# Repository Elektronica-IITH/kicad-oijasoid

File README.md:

# Elektronica Bootcamp '25 - README

## Overview
Welcome to Elektronica, the premier Electronics and Signal Processing Club at IIT Hyderabad! This README provides details about our Bootcamp '25, how to participate, what you can gain by joining us.

## About Elektronica
Elektronica is a vibrant community where technology enthusiasts collaborate on innovative projects, explore emerging tech trends, and engage in hands-on learning. From embedded systems and signal processing to wireless communication, we cover a broad spectrum of exciting domains.

## Why Join the Elektronica Bootcamp?
By participating in the Elektronica Bootcamp, you get access to:

- 🏆 **Skill Enhancement:** Gain hands-on experience in core electronics and signal processing domains.
- 🌟 **Expert-Led Sessions:** Learn from industry professionals and experienced mentors.
- 🤝 **Personalized Mentorship:** Receive guidance, clear your doubts, and enhance your technical skills.
- 🛠️ **Real-World Projects:** Work on practical projects that solve real-world problems.
- 🚀 **Innovative Learning:** Engage in interactive workshops and hackathons.

## Bootcamp Details
- **Start Date:** Mar 22, 2025
- **Duration:** 3 weeks (every Saturday, 5:30 - 7:30)

## Sessions
1. PCB Design
2. Biomedical signal processing
3. Sensors

## Final Project
Build a smartwatch as a team. 

## Contact Us
For queries or more information, feel free to reach out:
- **Email:** elektronica@gymkhana.iith.ac.in

Don't miss this chance to upskill and innovate with Elektronica!

Best Regards,  
**Elektronica**  
IIT Hyderabad

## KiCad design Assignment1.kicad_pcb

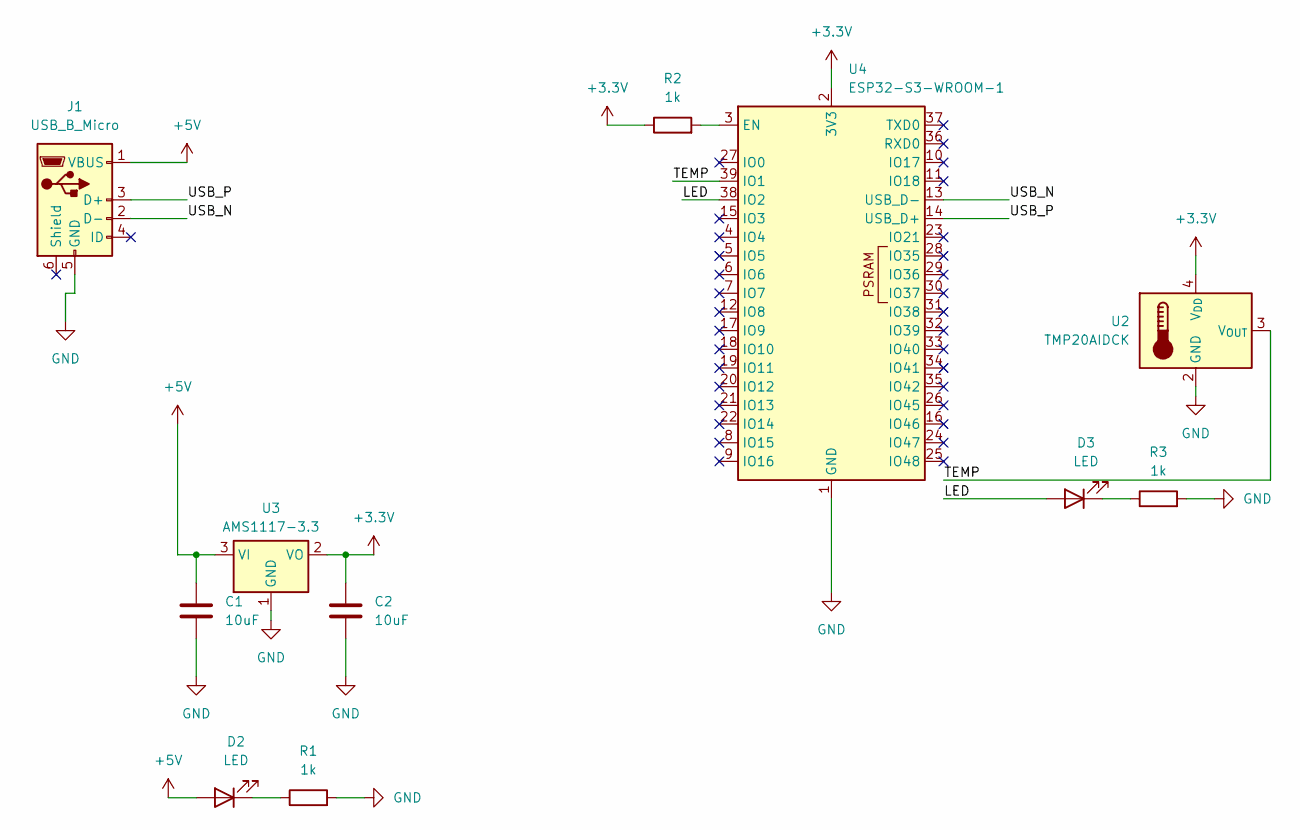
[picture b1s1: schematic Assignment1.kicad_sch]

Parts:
C1, C2: 10uF; C_0201_0603Metric
D2, D3: LED; LED_0201_0603Metric
J1: USB_B_Micro; USB_Micro-B_Amphenol_10118194-0001LF_Horizontal
R1, R2, R3: 1k; R_0201_0603Metric
U2: TMP20AIDCK; SOT-353_SC-70-5
U3: AMS1117-3.3; SOT-223-3_TabPin2
U4: ESP32-S3-WROOM-1

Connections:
+3.3V: C2.1, R2.1, U2.4 (V_{DD}), U3.2 (VO), U4.2 (3V3)
+5V: C1.1, D2.2 (A), J1.1 (VBUS), U3.3 (VI)
/LED: D3.2 (A), U4.38 (IO2)
/TEMP: U2.3 (V_{OUT}), U4.39 (IO1)
/USB_N: J1.2 (D-), U4.13 (USB_D-)
/USB_P: J1.3 (D+), U4.14 (USB_D+)
GND: C1.2, C2.2, J1.5 (GND), R1.2, R3.2, U2.2 (GND), U2.5 (GND), U3.1 (GND), U4.1 (GND), U4.40 (GND), U4.41 (GND)
unnamed: D2.1 (K), R1.1
unnamed: D3.1 (K), R3.1
unnamed: R2.2, U4.3 (EN)

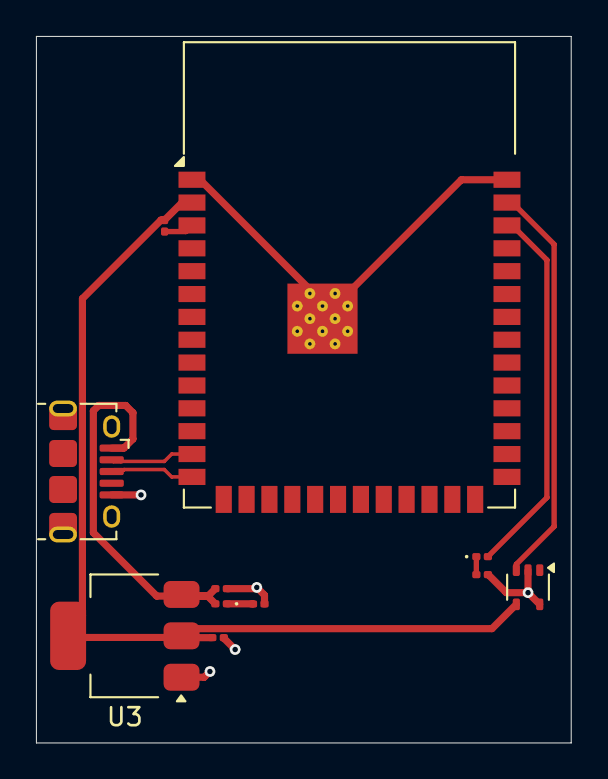
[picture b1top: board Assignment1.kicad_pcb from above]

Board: 2 copper layers, 29.7 x 39.2 mm, 11 parts (0 on the bottom side), 10 nets.

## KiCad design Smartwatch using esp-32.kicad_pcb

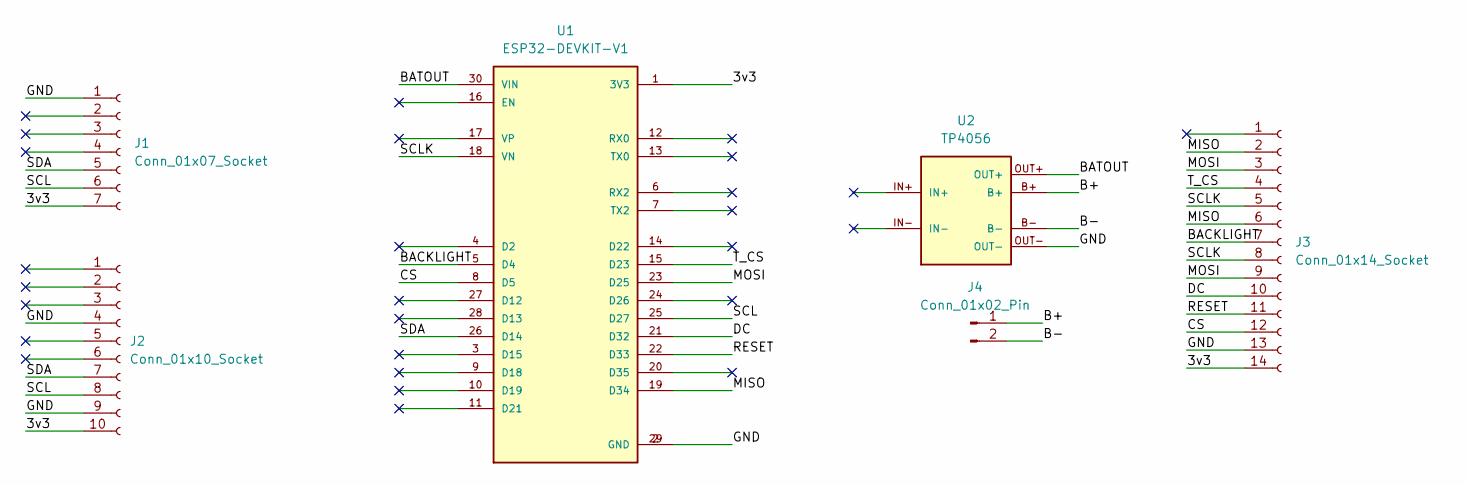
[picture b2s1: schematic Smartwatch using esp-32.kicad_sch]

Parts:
J1: Conn_01x07_Socket; PinSocket_1x07_P2.54mm_Vertical
J2: Conn_01x10_Socket; PinSocket_1x10_P2.54mm_Vertical
J3: Conn_01x14_Socket; PinSocket_1x14_P2.54mm_Vertical
J4: Conn_01x02_Pin; JST_PH_S2B-PH-K_1x02_P2.00mm_Horizontal
U1: ESP32-DEVKIT-V1; MODULE_ESP32_DEVKIT_V1; PARTREV N/A
U2: TP4056

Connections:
/3v3: J1.7, J2.10, J3.14, U1.1 (3V3)
/B+: J4.1, U2.B+
/B-: J4.2, U2.B-
/BACKLIGHT: J3.7, U1.5 (D4)
/BATOUT: U1.30 (VIN), U2.OUT+
/CS: J3.12, U1.8 (D5)
/DC: J3.10, U1.21 (D32)
/GND: J1.1, J2.4, J2.9, J3.13, U1.2 (GND), U1.29 (GND), U2.OUT-
/MISO: J3.2, J3.6, U1.19 (D34)
/MOSI: J3.3, J3.9, U1.23 (D25)
/RESET: J3.11, U1.22 (D33)
/SCL: J1.6, J2.8, U1.25 (D27)
/SCLK: J3.5, J3.8, U1.18 (VN)
/SDA: J1.5, J2.7, U1.26 (D14)
/T_CS: J3.4, U1.15 (D23)

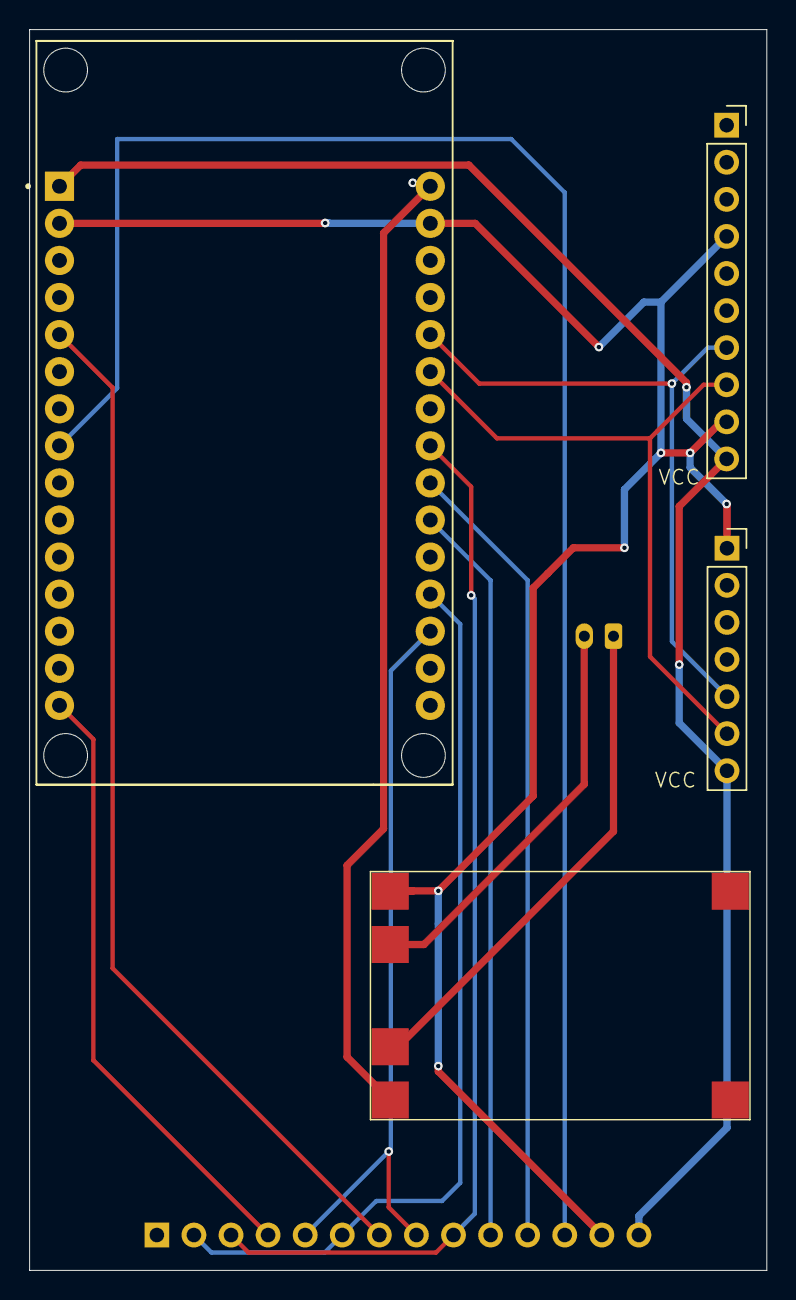
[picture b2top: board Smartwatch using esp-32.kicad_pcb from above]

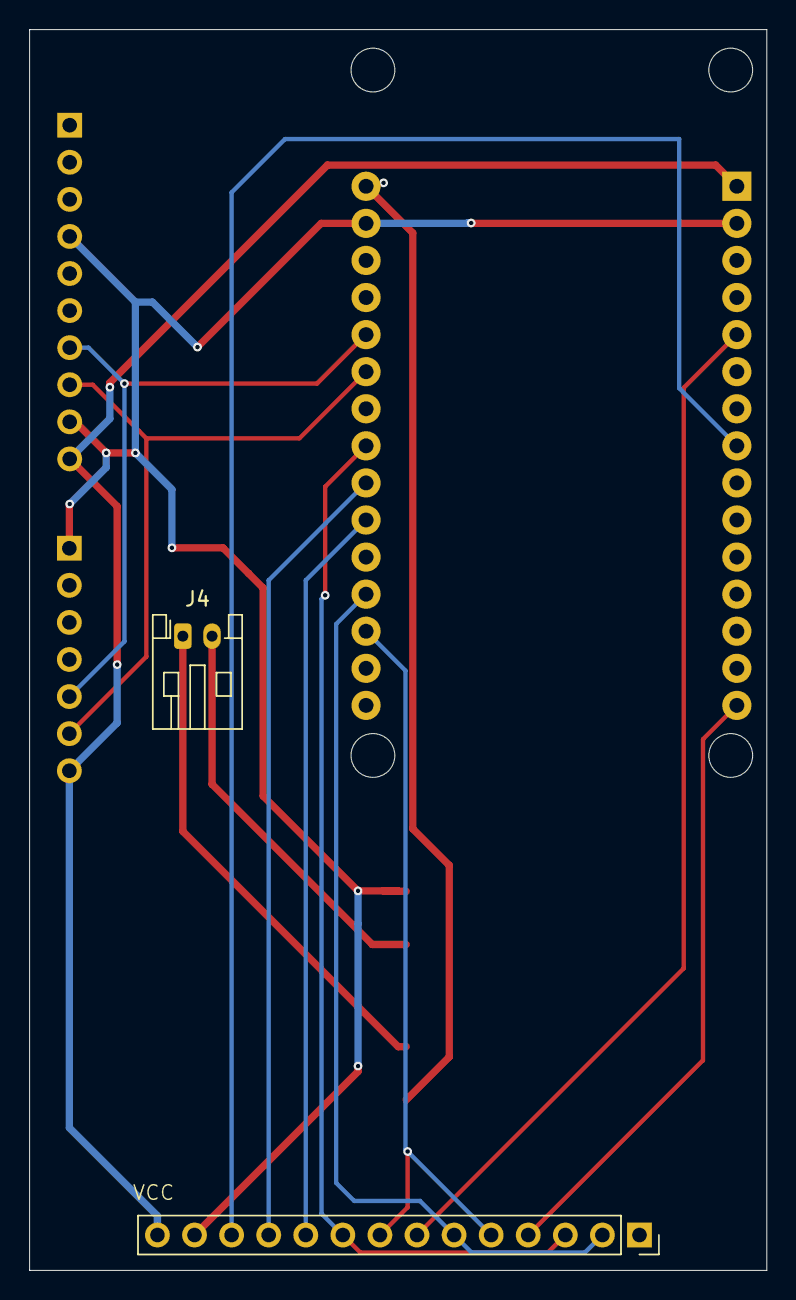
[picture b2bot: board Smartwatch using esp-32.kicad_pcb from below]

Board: 2 copper layers, 50.5 x 85.0 mm, 6 parts (2 on the bottom side), 15 nets.

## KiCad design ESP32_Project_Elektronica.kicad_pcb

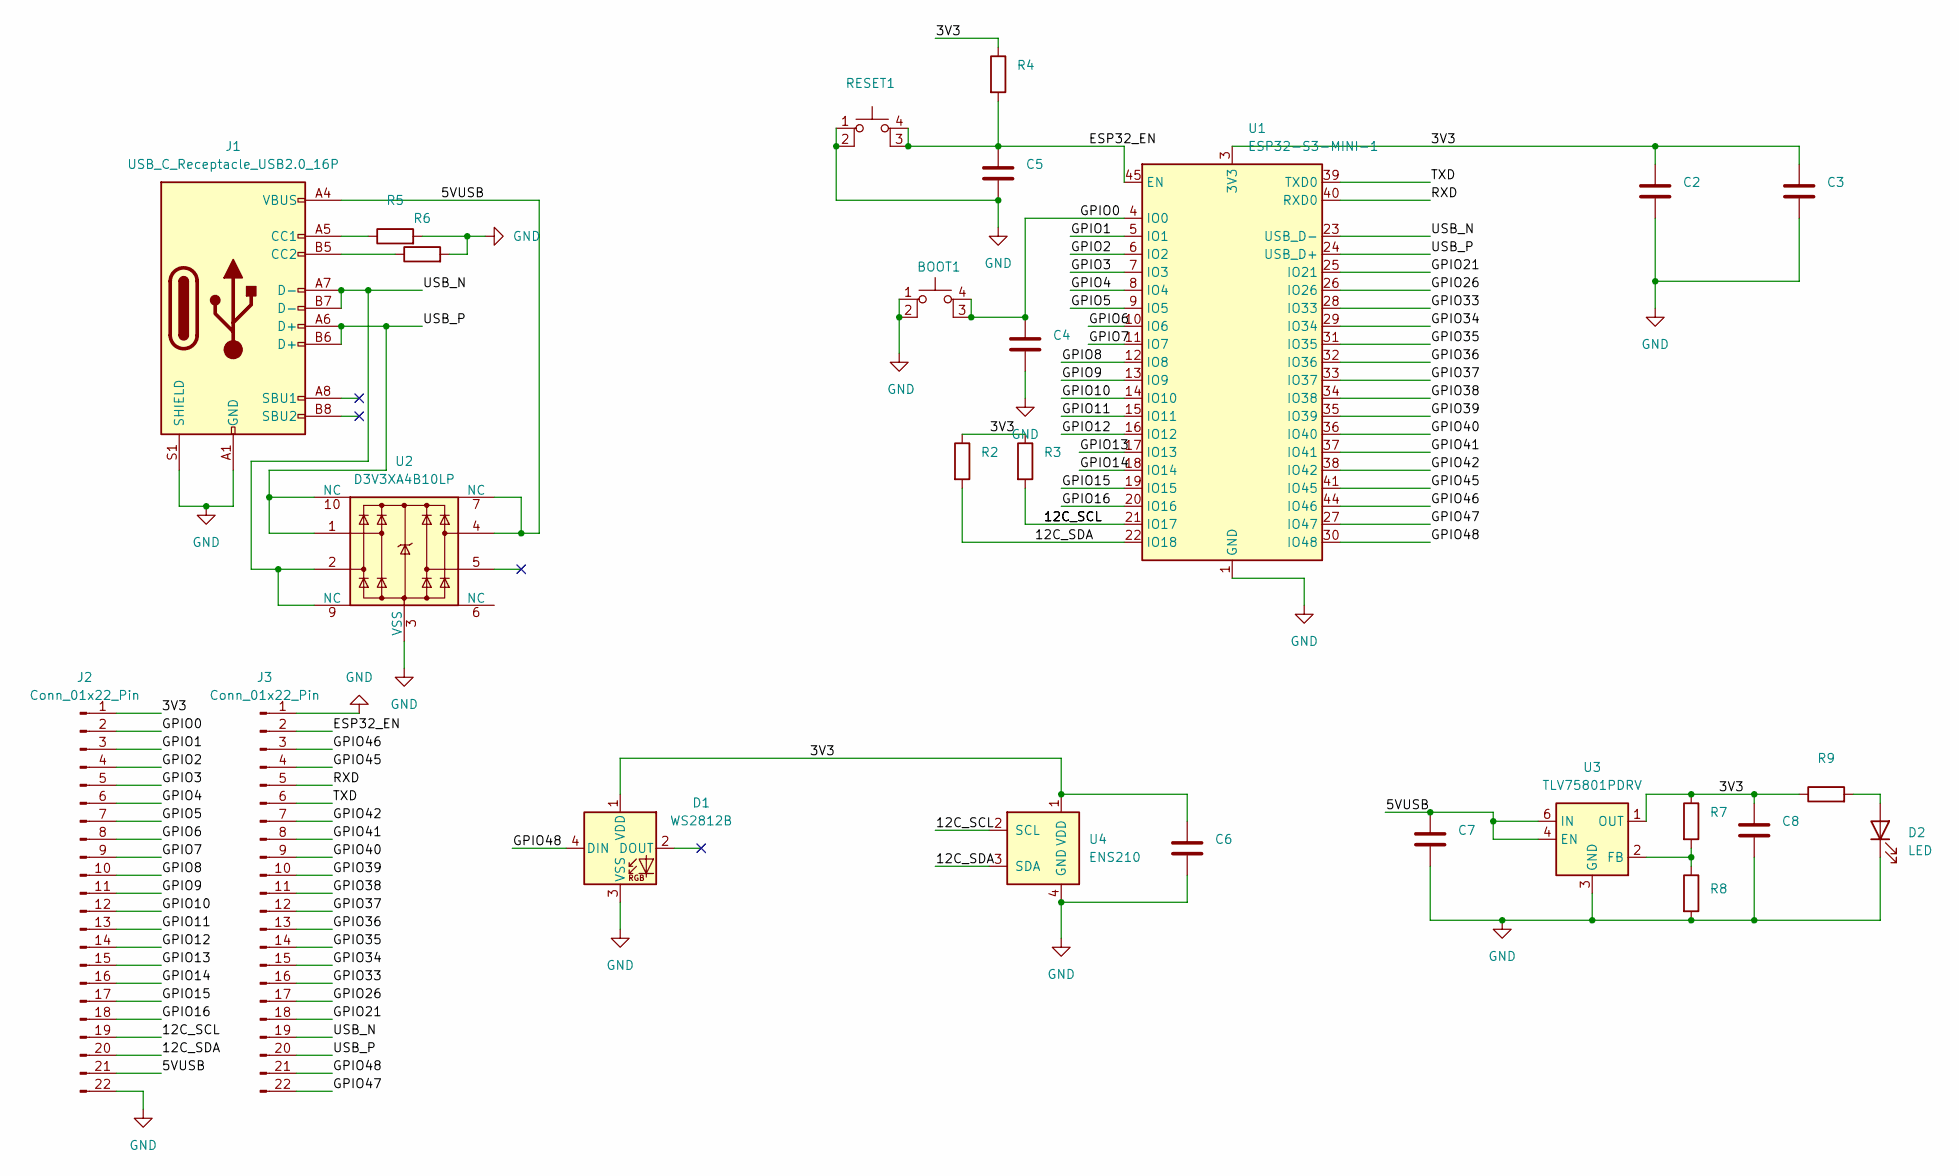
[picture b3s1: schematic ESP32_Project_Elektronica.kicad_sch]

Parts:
BOOT1: SW_MEC_5GSH9
C2, C3, C4, C5, C6, C7, C8: C_0603_1608Metric
D1: WS2812B; LED_WS2812B_PLCC4_5.0x5.0mm_P3.2mm
D2: LED; LED_0201_0603Metric_Pad0.64x0.40mm_HandSolder
J1: USB_C_Receptacle_USB2.0_16P; USB_C_Receptacle_GCT_USB4105-xx-A_16P_TopMnt_Horizontal
J2, J3: Conn_01x22_Pin; PinHeader_1x22_P2.54mm_Vertical
R2, R3, R4, R5, R6, R7, R8, R9: R_0603_1608Metric
RESET1: SW_MEC_5GSH9
U1: ESP32-S3-MINI-1; ESP32-S2-MINI-1
U2: D3V3XA4B10LP; Diodes_UDFN-10_1.0x2.5mm_P0.5mm
U3: TLV75801PDRV; WSON-6-1EP_2x2mm_P0.65mm_EP1x1.6mm
U4: ENS210; AMS_QFN-4-1EP_2x2mm_P0.95mm_EP0.7x1.6mm

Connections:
/3V3: C2.2, C3.2, C6.2, C8.2, D1.1 (VDD), J2.1, R2.1, R3.1, R4.1, R7.1, R9.1, U1.3 (3V3), U3.1 (OUT), U4.1 (VDD)
/5VUSB: C7.2, J1.A4 (VBUS), J1.A9 (VBUS), J1.B4 (VBUS), J1.B9 (VBUS), J2.21, U2.4, U2.7 (NC), U3.4 (EN), U3.6 (IN)
/12C_SDA: J2.20, R2.2, U1.22 (IO18), U4.3 (SDA)
/ESP32_EN: C5.2, J3.2, R4.2, RESET1.3 (K), RESET1.4 (A), U1.45 (EN)
/GPIO0: BOOT1.3 (K), BOOT1.4 (A), C4.2, J2.2, U1.4 (IO0)
/GPIO1: J2.3, U1.5 (IO1)
/GPIO2: J2.4, U1.6 (IO2)
/GPIO3: J2.5, U1.7 (IO3)
/GPIO4: J2.6, U1.8 (IO4)
/GPIO5: J2.7, U1.9 (IO5)
/GPIO6: J2.8, U1.10 (IO6)
/GPIO7: J2.9, U1.11 (IO7)
/GPIO8: J2.10, U1.12 (IO8)
/GPIO9: J2.11, U1.13 (IO9)
/GPIO10: J2.12, U1.14 (IO10)
/GPIO11: J2.13, U1.15 (IO11)
/GPIO12: J2.14, U1.16 (IO12)
/GPIO13: J2.15, U1.17 (IO13)
/GPIO14: J2.16, U1.18 (IO14)
/GPIO15: J2.17, U1.19 (IO15)
/GPIO16: J2.18, U1.20 (IO16)
/GPIO21: J3.18, U1.25 (IO21)
/GPIO26: J3.17, U1.26 (IO26)
/GPIO33: J3.16, U1.28 (IO33)
/GPIO34: J3.15, U1.29 (IO34)
/GPIO35: J3.14, U1.31 (IO35)
/GPIO36: J3.13, U1.32 (IO36)
/GPIO37: J3.12, U1.33 (IO37)
/GPIO38: J3.11, U1.34 (IO38)
/GPIO39: J3.10, U1.35 (IO39)
/GPIO40: J3.9, U1.36 (IO40)
/GPIO41: J3.8, U1.37 (IO41)
/GPIO42: J3.7, U1.38 (IO42)
/GPIO45: J3.4, U1.41 (IO45)
/GPIO46: J3.3, U1.44 (IO46)
/GPIO47: J3.22, U1.27 (IO47)
/GPIO48: D1.4 (DIN), J3.21, U1.30 (IO48)
/RXD: J3.5, U1.40 (RXD0)
/TXD: J3.6, U1.39 (TXD0)
/USB_N: J1.A7 (D-), J1.B7 (D-), J3.19, U1.23 (USB_D-), U2.2, U2.9 (NC)
/USB_P: J1.A6 (D+), J1.B6 (D+), J3.20, U1.24 (USB_D+), U2.1, U2.10 (NC)
GND: BOOT1.1, BOOT1.2, C2.1, C3.1, C4.1, C5.1, C6.1, C7.1, C8.1, D1.3 (VSS), D2.1 (K), J1.A1 (GND), J1.A12 (GND), J1.B1 (GND), J1.B12 (GND), J1.S1 (SHIELD), J2.22, J3.1, R5.2, R6.2, R8.2, RESET1.1, RESET1.2, U1.1 (GND), U1.2 (GND), U1.42 (GND), U1.43 (GND), U1.46 (GND), U1.47 (GND), U1.48 (GND), U1.49 (GND), U1.50 (GND), U1.51 (GND), U1.52 (GND), U1.53 (GND), U1.54 (GND), U1.55 (GND), U1.56 (GND), U1.57 (GND), U1.58 (GND), U1.59 (GND), U1.60 (GND), U1.61 (GND), U1.62 (GND), U1.63 (GND), U1.64 (GND), U1.65 (GND), U2.3 (VSS), U2.8 (VSS), U3.3 (GND), U3.7 (GND), U4.4 (GND), U4.5 (GND)
unnamed: D2.2 (A), R9.2
unnamed: J1.A5 (CC1), R5.1
unnamed: J1.B5 (CC2), R6.1
unnamed: R7.2, R8.1, U3.2 (FB)

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
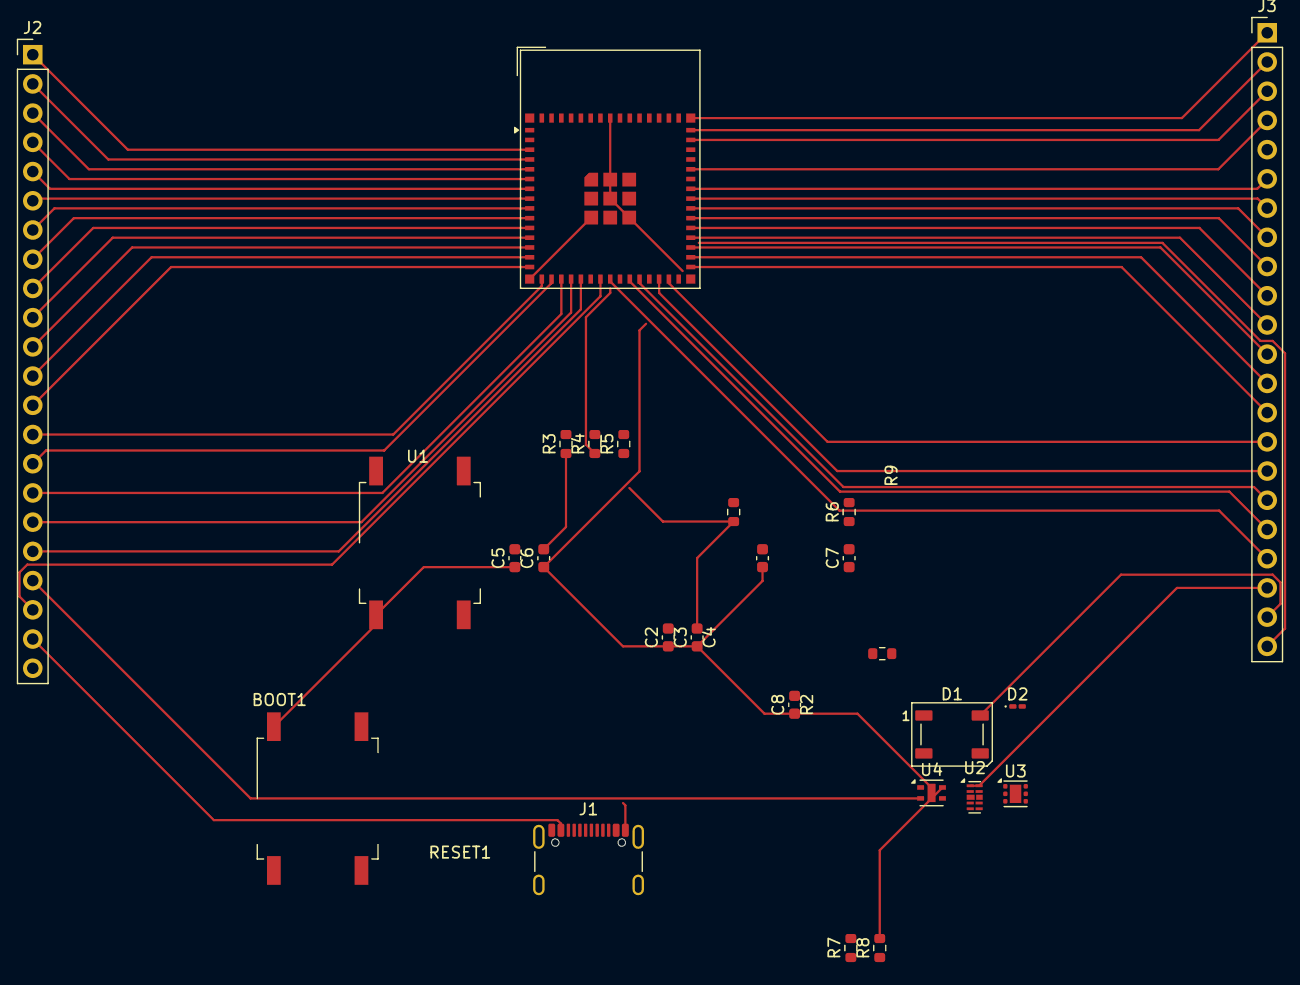
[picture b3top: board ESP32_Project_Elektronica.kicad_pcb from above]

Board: 2 copper layers, 26 parts (0 on the bottom side), 48 nets.

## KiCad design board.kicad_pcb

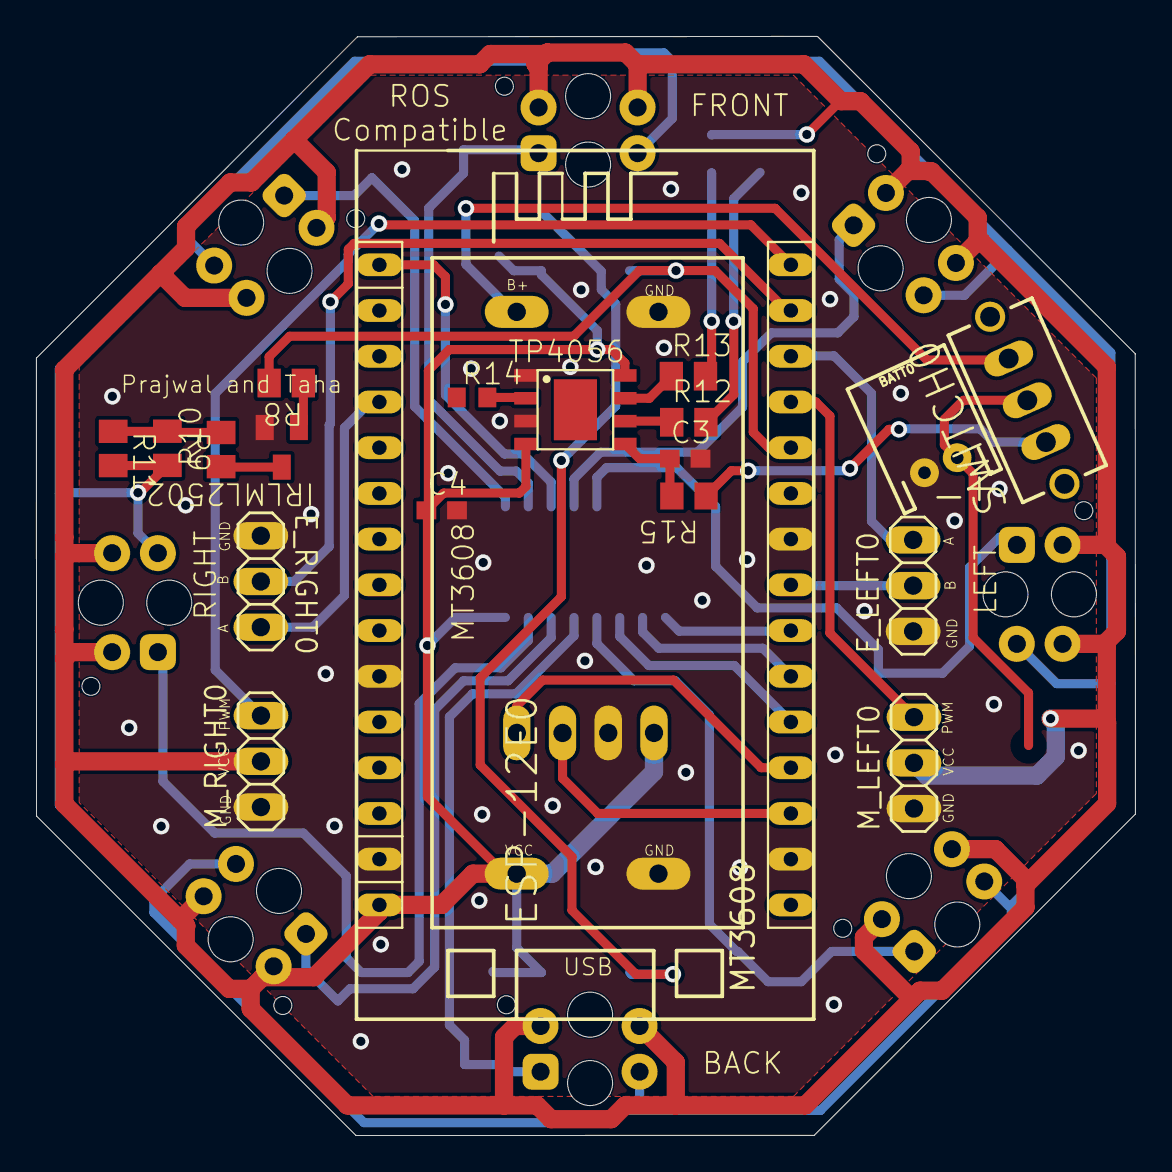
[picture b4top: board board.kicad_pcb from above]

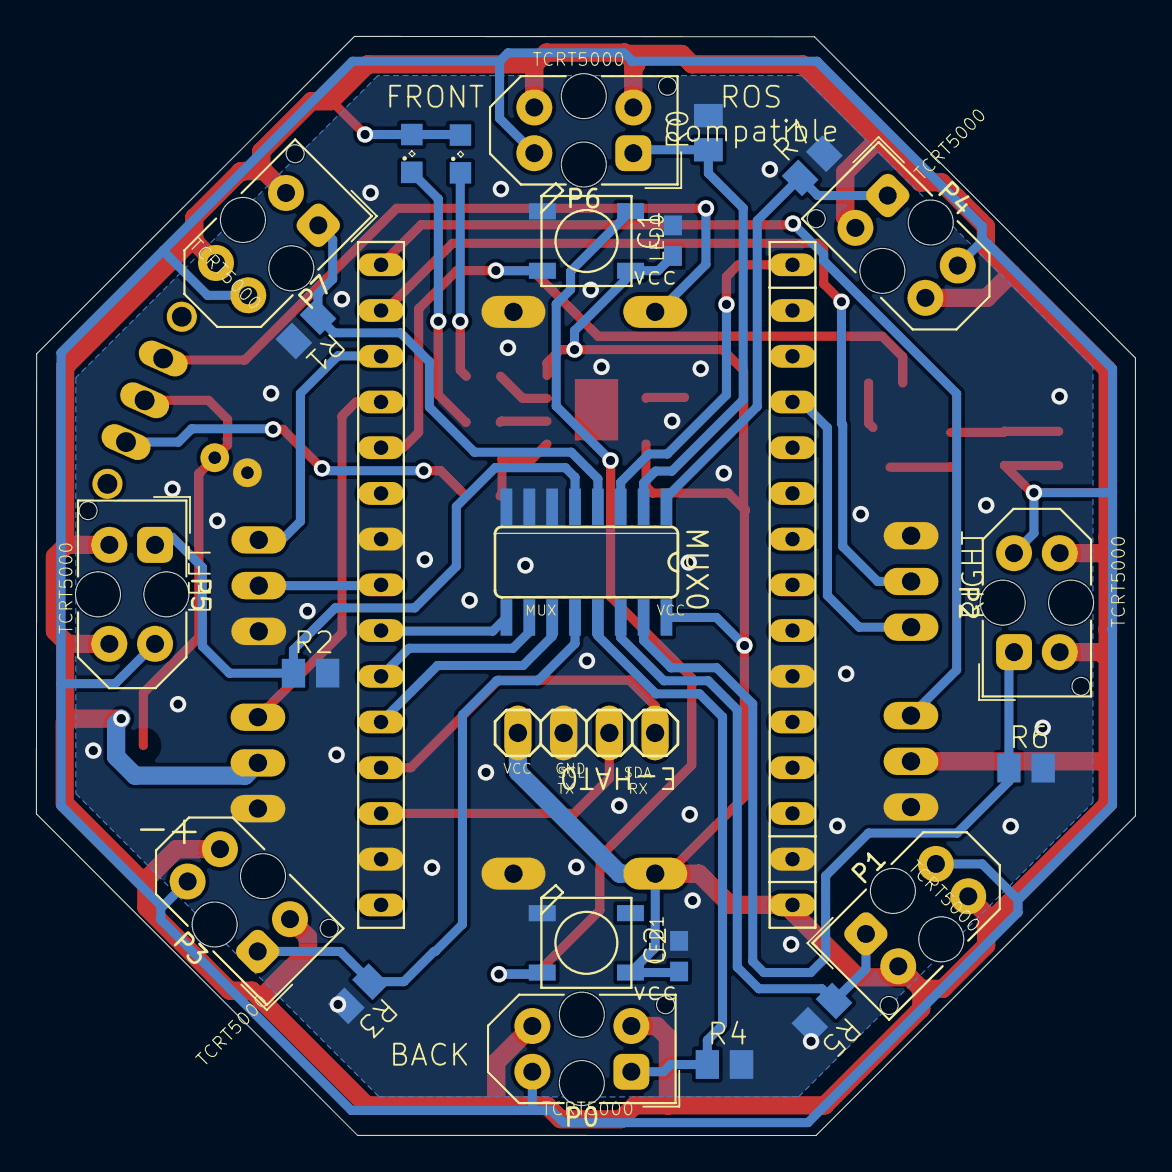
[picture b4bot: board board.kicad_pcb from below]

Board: 2 copper layers, 61.1 x 61.1 mm, 44 parts (24 on the bottom side), 37 nets.

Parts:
BATT0: CONN_02JST-PTH-2; JST-2-PTH_513
C1, C2: 0.10 nF; C0603_348
C3, C4: 10 uF; C0603_420
CHRG0: RED; SML0805_259
E-HAT0: PINHD-1X4; 1X04
ESP-12E0: ESP12E_DEVKIT
E_LEFT0: PINHD-1X3; 1X03
E_RIGHT0: PINHD-1X3; 1X03
IRLML2502: MOSFET-NREFLOW; SOT23_420
LED0, LED1: WS2812B5050; WS2812B_420
MT3608: MT3608
MUX0: 4051D; SO16_80
M_LEFT0: PINHD-1X3; 1X03
M_RIGHT0: PINHD-1X3; 1X03
P0, P1, P2, P3, P4, P5, P6, P7: Vishay_TCRT5000
R0, R1, R2, R3, R4, R5, R6, R7, R8: 4k7; M0805_420
R9: 0R; M0805_420
R10: 18R; M0805_420
R11: NM; M0805_420
R12: 103; M0805_420
R13: 102; M0805_420
R14: 122; R0603_348
R15: 0R; R0805_348
STDBY0: GREEN; SML0805_259
SWITCH0: SS12F2356; HH3T90
TP4056: TP4056; SOP-8

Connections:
/<p>MCU and Motors</p>/E_LEFT_A: ESP-12E0.D2, E_LEFT0.3
/<p>MCU and Motors</p>/E_LEFT_B: ESP-12E0.D5, E_LEFT0.2
/<p>MCU and Motors</p>/E_RIGHT_A: ESP-12E0.SD3, E_RIGHT0.3
/<p>MCU and Motors</p>/E_RIGHT_B: ESP-12E0.D1, E_RIGHT0.2
/<p>MCU and Motors</p>/M_LEFT_PWM: ESP-12E0.D3, M_LEFT0.3
/<p>MCU and Motors</p>/M_RIGHT_PWM: ESP-12E0.D0, M_RIGHT0.3
/<p>MCU and Motors</p>/SCL_TX: E-HAT0.2, ESP-12E0.TX
/<p>MCU and Motors</p>/SDA_RX: E-HAT0.1, ESP-12E0.RX
/<p>Power Supply</p>/TP_B+: C3.1, R15.2, TP4056.5 (BAT)
/<p>Proximity Sensors</p>/EM: P0.4, P1.4, P2.4, P3.4, P4.4, P5.4, P6.4, P7.4, R9.2, R11.2
/<p>Proximity Sensors</p>/MUX_X0: MUX0.13 (X0), P0.1, R4.1
/<p>Proximity Sensors</p>/MUX_X1: MUX0.14 (X1), P1.1, R5.1
/<p>Proximity Sensors</p>/MUX_X2: MUX0.15 (X2), P2.1, R6.1
/<p>Proximity Sensors</p>/MUX_X3: MUX0.12 (X3), P3.1, R3.1
/<p>Proximity Sensors</p>/MUX_X4: MUX0.1 (X4), P4.1, R7.1
/<p>Proximity Sensors</p>/MUX_X5: MUX0.5 (X5), P5.1, R2.1
/<p>Proximity Sensors</p>/MUX_X6: MUX0.2 (X6), P6.1, R0.1
/<p>Proximity Sensors</p>/MUX_X7: MUX0.4 (X7), P7.1, R1.1
AD0: ESP-12E0.AD0, MUX0.3 (X)
EM_ENABLE: ESP-12E0.D4, LED0.4-DIN (DI), R8.2
GND: BATT0.1, C1.2, C2.2, C3.2, C4.2, E-HAT0.3, ESP-12E0.GND@0, ESP-12E0.GND@1, ESP-12E0.GND@2, ESP-12E0.GND@3, E_LEFT0.1, E_RIGHT0.1, IRLML2502.2 (S), LED0.3-GND (GND), LED1.3-GND (GND), MT3608.B-, MT3608.GND, MUX0.6 (INH), MUX0.7 (VEE), MUX0.8 (GND), M_LEFT0.1, M_RIGHT0.1, R0.2, R1.2, R2.2, R3.2, R4.2, R5.2, R6.2, R7.2, TP4056.1 (TEMP), TP4056.3 (GND)
MUX_A: ESP-12E0.D8, MUX0.11 (A)
MUX_B: ESP-12E0.D7, MUX0.10 (B)
MUX_C: ESP-12E0.D6, MUX0.9 (C)
unnamed: CHRG0.C, R13.2
unnamed: IRLML2502.3 (D), R10.1
unnamed: IRLML2502.1 (G), R8.1
unnamed: LED0.2-DOUT (DO), LED1.4-DIN (DI)
unnamed: R9.1, R10.2, R11.1
unnamed: R12.2, STDBY0.C
unnamed: R15.1, SWITCH0.1 (O)
unnamed: BATT0.2, SWITCH0.2
unnamed: MT3608.B+, SWITCH0.3 (S)
unnamed: R13.1, TP4056.7 (CHRG)
unnamed: R14.2, TP4056.2 (PROG)
unnamed: R12.1, TP4056.6 (STDBY)
VCC: C1.1, C2.1, C4.1, CHRG0.A, E-HAT0.4, ESP-12E0.VIN, LED0.1-VDD (VDD), LED1.1-VDD (VDD), MT3608.5V, MUX0.16 (VCC), M_LEFT0.2, M_RIGHT0.2, P0.2, P0.3, P1.2, P1.3, P2.2, P2.3, P3.2, P3.3, P4.2, P4.3, P5.2, P5.3, P6.2, P6.3, P7.2, P7.3, STDBY0.A, TP4056.4 (VCC), TP4056.8 (CE)

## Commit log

2025-03-14 Create GitHub Classroom Autograding Workflow
2025-03-14 Automated PCB Check Results: Score 50/100
2025-03-14 Rename classroom.yml to workflow.yml
2025-03-14 GitHub Classroom Autograding Workflow
2025-03-14 add deadline
2025-03-14 Automated PCB Check Results: Score 100/100
2025-03-14 sanjs
2025-03-14 Update autograding workflow
2025-03-15 Automated PCB Check: Score 100/100
2025-03-20 [+] Check for ESP32 and autograde
2025-03-20 Automated PCB Check: Score 50/100
2025-03-20 clean repo
2025-03-20 Create dummy
2025-03-20 [.] all set
2025-03-29 Added Assignment-1 files
2025-03-29 Added Espressif library zip
2025-03-29 adding Signal Processing files
2025-03-29 correcting naming
2025-03-29 adding signal files
2025-03-29 [.] checking workflow by Prajwal
2025-03-29 Rename Assignment-1.kicad_pcb to Assignment1.kicad_pcb
2025-03-29 Rename Assignment-1.kicad_sch to Assignment1.kicad_sch
2025-03-29 Assignment 1 submission
2025-03-29 testing
2025-03-29 Automated PCB Check: Score 0/100
2025-03-29 Automated PCB Check: Score 98/100
2025-03-29 adding signal_proc
2025-03-29 [+] fix
2025-04-05 add week 3 codes
2025-04-05 add session slides
2025-04-05 Added Assignment-2 files
2025-04-05 add ldr
